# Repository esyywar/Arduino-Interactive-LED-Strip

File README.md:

# Arduino-Interactive-LED-Strip

This project features the hardware and software development of a multi-function LED strip controller!

The light strip has 3 different modes:
1. HSV Static Colour Set
2. Patterned Light Show
3. Music Wave Visualizer

User can switch between the 3 modes by pushing a button. In each mode, parameters can be adjusted by turning the 3 potentiometer knobs.

Here are the functions of each knob in each mode:

| Mode  | Knob 1 | Knob 2 | Knob 3 |
| -------- | ---- | ---- | ---- |
| HSV Static Colour Set | Hue | Saturation | Brightness |
| Patterned Light Show | Colour Pattern | Scramble Effect | Brightness |
| Music Wave Visualizer | Wave Point Source | Volume Sensitivity | Brightness |

Folders in the repository are organized as follows:

## Firmware

The arduino nano code for this controller. Simple code using FastLED library and interrupts for switching modes.

## PCB-Design

PCB designed in KiCAD to recreate this controller
Can be assembled for about 40 - 80 CAD depending on how much you spend for PCB fabrication and the LED strip.

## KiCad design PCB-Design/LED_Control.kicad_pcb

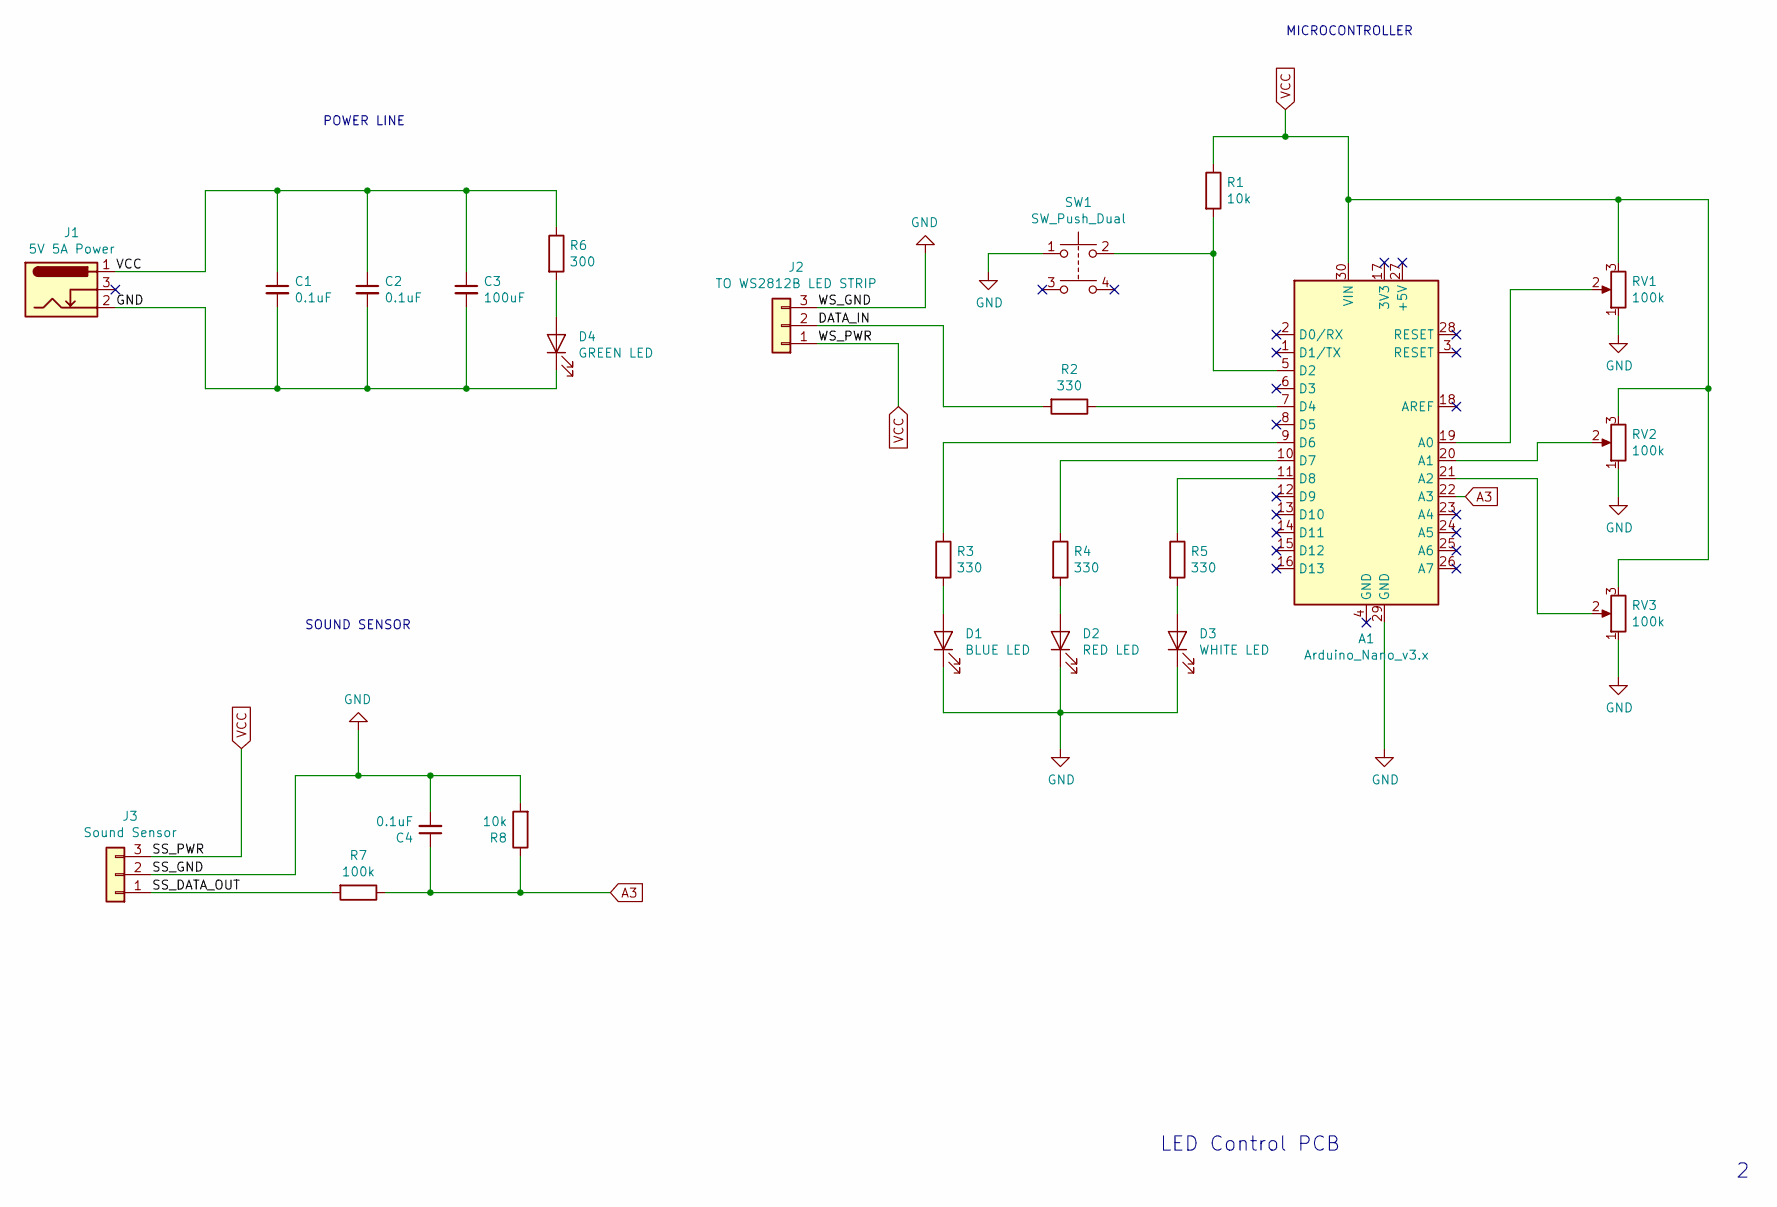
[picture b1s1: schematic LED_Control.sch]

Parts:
A1: Arduino_Nano_v3.x; Arduino_Nano
C1: 0.1uF; C_0603_1608Metric; LCSC C14663
C2: 0.1uF; C_0603_1608Metric; LCSC C15849
C3: 100uF; CP_EIA-3528-15_AVX-H; LCSC C16133
C4: 0.1uF; C_Disc_D3.4mm_W2.1mm_P2.50mm
D1: BLUE LED; LED_D5.0mm
D2: RED LED; LED_D5.0mm
D3: WHITE LED; LED_D5.0mm
D4: GREEN LED; LED_0805_2012Metric; LCSC C63855
J1: 5V 5A Power; CUI_PJ-002AH
J2: TO WS2812B LED STRIP; TerminalBlock_TE_282834-3_1x03_P2.54mm_Horizontal
J3: Sound Sensor; TerminalBlock_TE_282834-3_1x03_P2.54mm_Horizontal
R1: 10k; R_0805_2012Metric; LCSC C17414
R2, R3, R4, R5: 330; R_0805_2012Metric; LCSC C17630
R6: 300; R_0805_2012Metric; LCSC C17617
R7: 100k; R_Axial_DIN0204_L3.6mm_D1.6mm_P5.08mm_Horizontal
R8: 10k; R_Axial_DIN0204_L3.6mm_D1.6mm_P5.08mm_Horizontal
RV1, RV2, RV3: 100k; Potentiometer_5.08mm_Pitch
SW1: SW_Push_Dual; Push_Button_Switch

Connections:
/DATA_IN: J2.2, R2.2
/SS_DATA_OUT: J3.1, R7.2
A3: A1.22 (A3), C4.1, R7.1, R8.1
GND: A1.29 (GND), C1.2, C2.2, C3.2, C4.2, D1.1 (K), D2.1 (K), D3.1 (K), D4.1 (K), J1.2, J2.3, J3.2, R8.2, RV1.1, RV2.1, RV3.1, SW1.1
unnamed: A1.5 (D2), R1.2, SW1.2
unnamed: A1.7 (D4), R2.1
unnamed: A1.9 (D6), R3.1
unnamed: A1.10 (D7), R4.1
unnamed: A1.11 (D8), R5.1
unnamed: A1.19 (A0), RV1.2
unnamed: A1.20 (A1), RV2.2
unnamed: A1.21 (A2), RV3.2
unnamed: D1.2 (A), R3.2
unnamed: D2.2 (A), R4.2
unnamed: D3.2 (A), R5.2
unnamed: D4.2 (A), R6.2
VCC: A1.30 (VIN), C1.1, C2.1, C3.1, J1.1, J2.1, J3.3, R1.1, R6.1, RV1.3, RV2.3, RV3.3

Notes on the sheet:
MICROCONTROLLER
SOUND SENSOR
POWER LINE
LED Control PCB

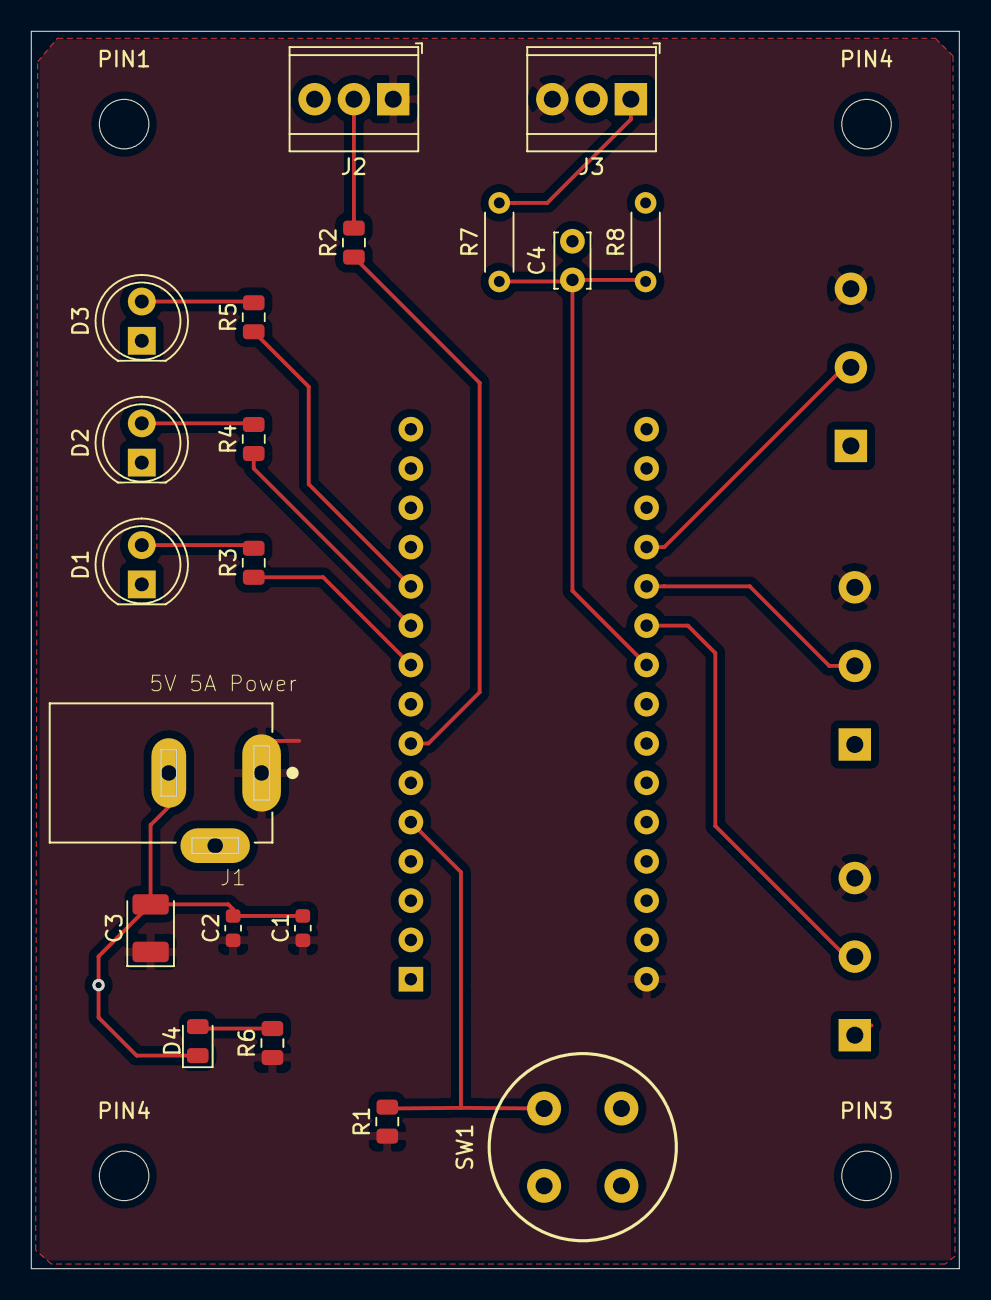
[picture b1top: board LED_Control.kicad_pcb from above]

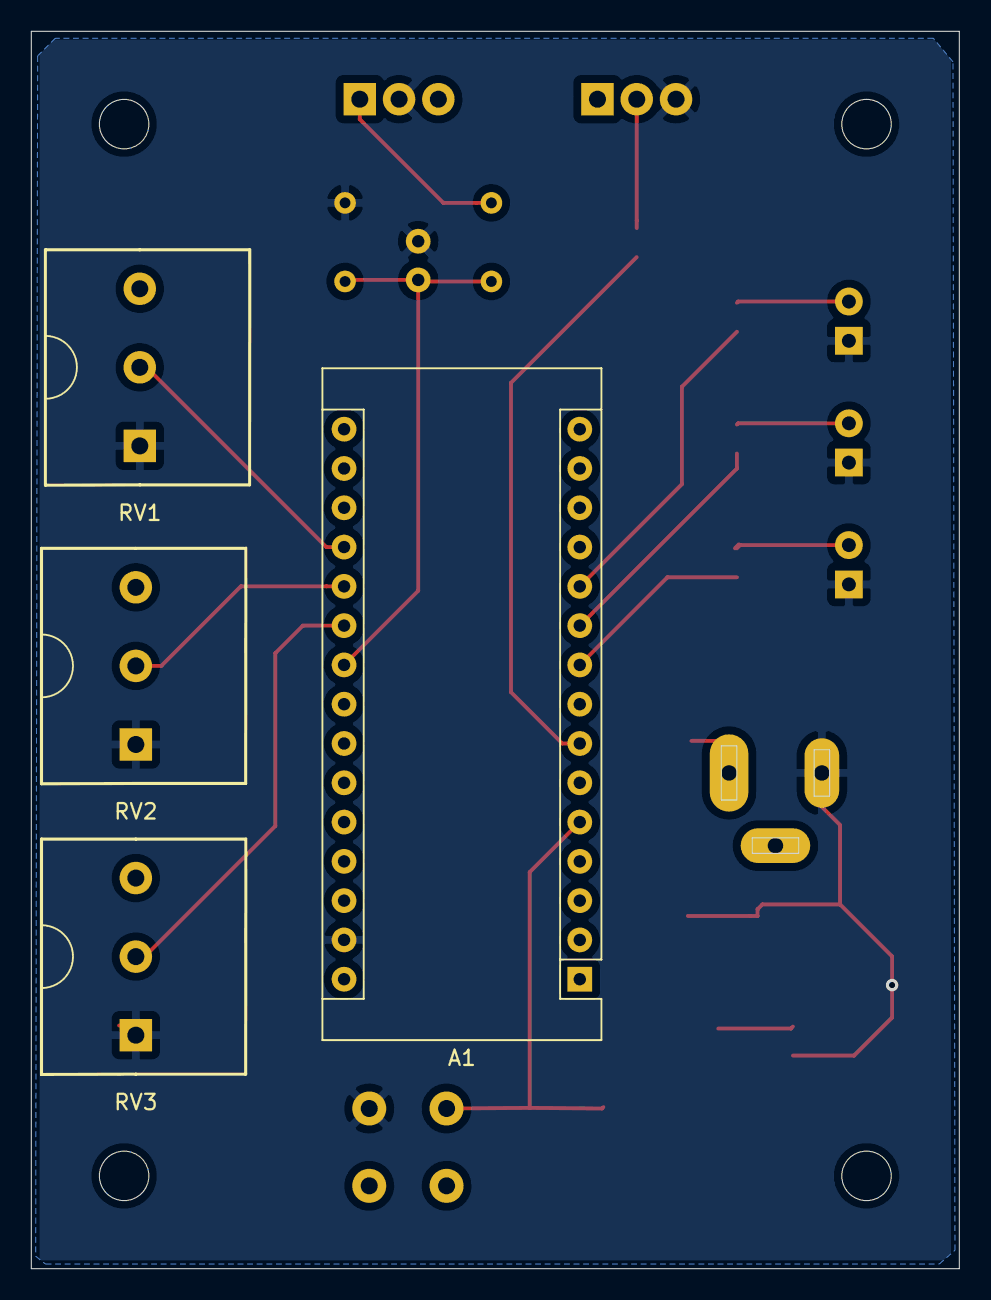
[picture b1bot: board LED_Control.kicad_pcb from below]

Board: 2 copper layers, 60.0 x 80.0 mm, 28 parts (4 on the bottom side), 17 nets.

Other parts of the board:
PIN1, PIN3, PIN4, PIN4#2: M3 HOLE; MountingHole_3.2mm_M3

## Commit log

2020-01-25 added point source wave
2020-01-25 integrating music visualizer into main...
2020-01-25 programs merged but bug with colour interval in visualizer
2020-01-25 typo corrected
2020-01-25 code clean up
2020-01-26 clean up main code
2020-01-26 memory issue identified - variable sizes optimized
2020-01-26 completed firmware - brightness control added to music visualizer
2020-01-26 bug found with mode change - save working version
2020-01-26 all bugs resolved and tested
2020-01-28 circuit schematic complete
2020-01-30 PCB footprints added
2020-02-08 connectors selected and footprints updated
2020-02-08 capacitor footprints changed to axial
2020-02-08 Rs, Cs, LED updated for SMT
2020-02-11 pull up/down resistors added
2020-02-11 pcb layout created
2020-02-11 pcb size made 60x60
2020-02-12 firmware adjusted for voltage divider and filter at sound sensor
2020-02-13 firmware bug found and corrected
2020-02-24 edge cuts and M3 mounting holes added
2020-02-26 microcontroller moved to bottom side
2020-02-28 power, gnd planes and traces
2020-02-29 PCB completed
2020-02-29 gerbers generated
2020-02-29 CPL and BOM generated
2020-03-01 CPL and BOM file format set
2020-03-01 final submitted build files
2020-03-13 potentiometer footprint fixed
2020-03-13 origin select for music vis. fix
2020-03-17 Rev 2. alterations to PCB
2020-03-22 global struct to save RAM
2020-05-14 firmware potentiometer range corrected for pcb impedances
2020-05-14 adjusted thresholds for pcb impedances
2020-05-16 pattern mode pot modes adjusted
2020-05-23 strip extended
2020-05-23 pic added
2020-05-23 photo edited
2020-06-06 img update
